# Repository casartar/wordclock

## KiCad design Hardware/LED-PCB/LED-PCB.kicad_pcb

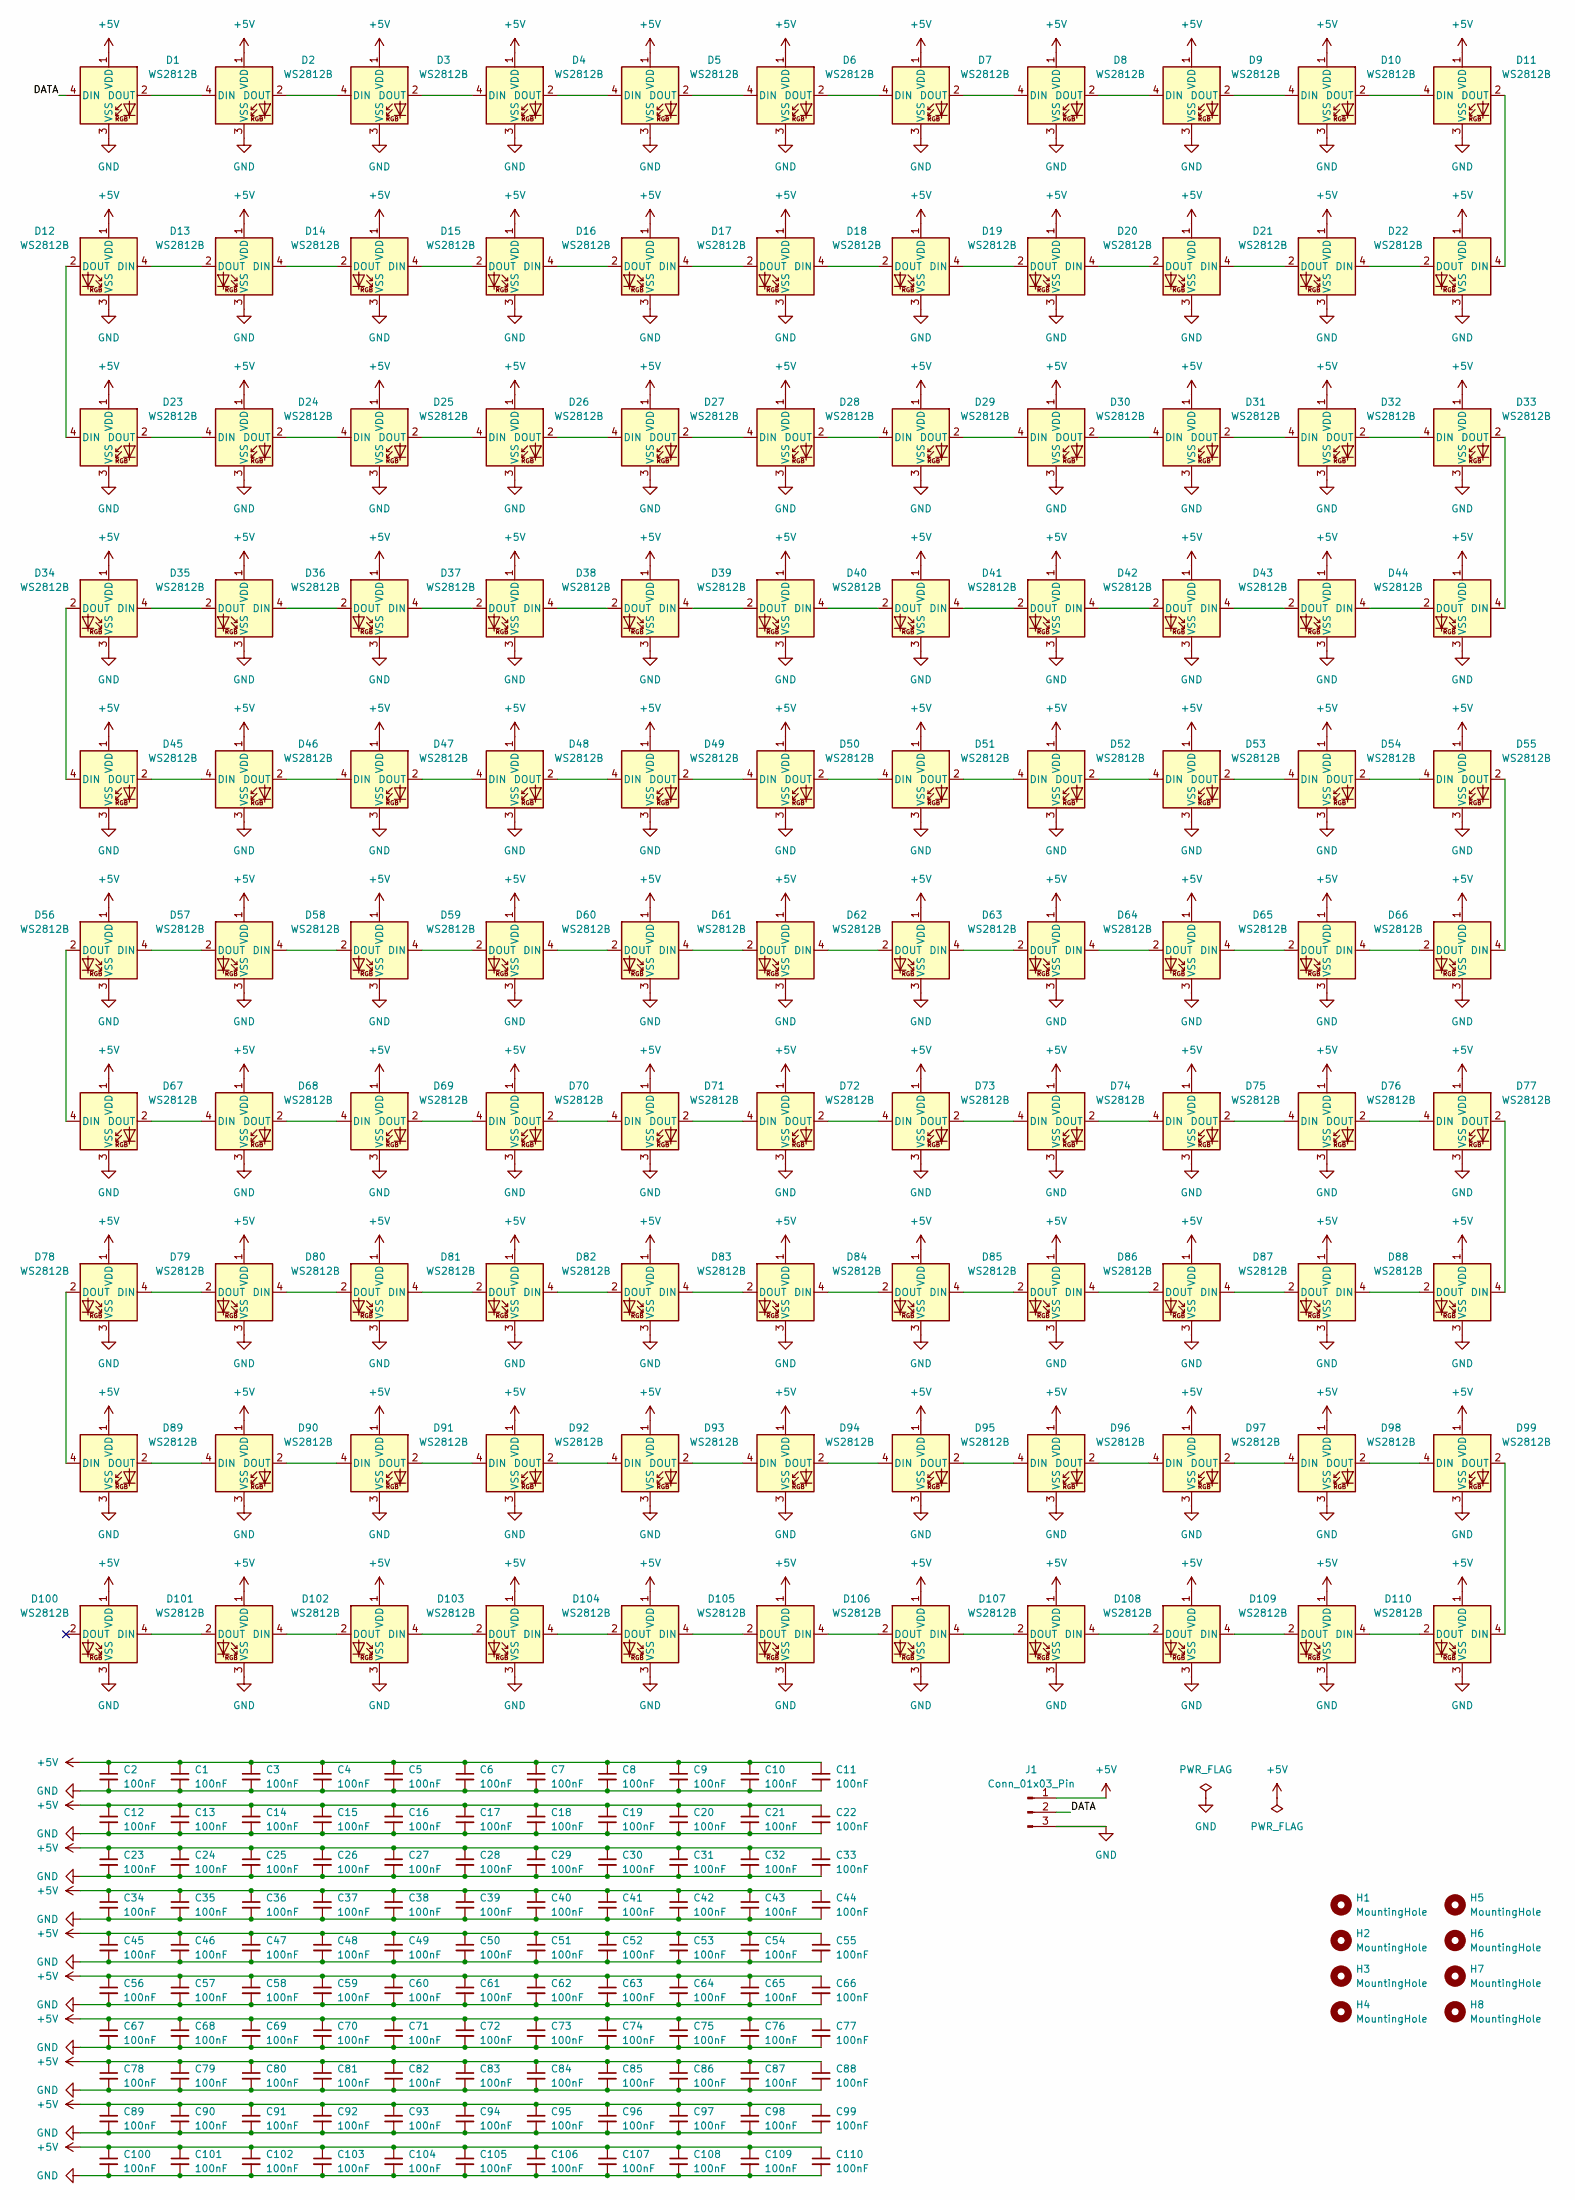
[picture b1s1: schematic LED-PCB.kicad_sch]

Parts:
C1, C2, C3, C4, C5, C6, C7, C8, C9, C10, C11, C12, C13, C14, C15, C16, C17, C18, C19, C20, C21, C22, C23, C24, C25, C26, C27, C28, C29, C30, C31, C32, C33, C34, C35, C36, C37, C38, C39, C40, C41, C42, C43, C44, C45, C46, C47, C48, C49, C50, C51, C52, C53, C54, C55, C56, C57, C58, C59, C60, C61, C62, C63, C64, C65, C66, C67, C68, C69, C70, C71, C72, C73, C74, C75, C76, C77, C78, C79, C80, C81, C82, C83, C84, C85, C86, C87, C88, C89, C90, C91, C92, C93, C94, C95, C96, C97, C98, C99, C100, C101, C102, C103, C104, C105, C106, C107, C108, C109, C110: 100nF; C_0805_2012Metric_Pad1.18x1.45mm_HandSolder
D1, D2, D3, D4, D5, D6, D7, D8, D9, D10, D11, D12, D13, D14, D15, D16, D17, D18, D19, D20, D21, D22, D23, D24, D25, D26, D27, D28, D29, D30, D31, D32, D33, D34, D35, D36, D37, D38, D39, D40, D41, D42, D43, D44, D45, D46, D47, D48, D49, D50, D51, D52, D53, D54, D55, D56, D57, D58, D59, D60, D61, D62, D63, D64, D65, D66, D67, D68, D69, D70, D71, D72, D73, D74, D75, D76, D77, D78, D79, D80, D81, D82, D83, D84, D85, D86, D87, D88, D89, D90, D91, D92, D93, D94, D95, D96, D97, D98, D99, D100, D101, D102, D103, D104, D105, D106, D107, D108, D109, D110: WS2812B; LED_WS2812B_PLCC4_5.0x5.0mm_P3.2mm
H1, H2, H3, H4, H5, H6, H7, H8: MountingHole; MountingHole_3.2mm_M3
J1: Conn_01x03_Pin; HDR-SMD_3P-P2.54-H-M_KH-2.54PH-1X3P-L13.5-WT

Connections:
+5V: C1.1, C2.1, C3.1, C4.1, C5.1, C6.1, C7.1, C8.1, C9.1, C10.1, C11.1, C12.1, C13.1, C14.1, C15.1, C16.1, C17.1, C18.1, C19.1, C20.1, C21.1, C22.1, C23.1, C24.1, C25.1, C26.1, C27.1, C28.1, C29.1, C30.1, C31.1, C32.1, C33.1, C34.1, C35.1, C36.1, C37.1, C38.1, C39.1, C40.1, C41.1, C42.1, C43.1, C44.1, C45.1, C46.1, C47.1, C48.1, C49.1, C50.1, C51.1, C52.1, C53.1, C54.1, C55.1, C56.1, C57.1, C58.1, C59.1, C60.1, C61.1, C62.1, C63.1, C64.1, C65.1, C66.1, C67.1, C68.1, C69.1, C70.1, C71.1, C72.1, C73.1, C74.1, C75.1, C76.1, C77.1, C78.1, C79.1, C80.1, C81.1, C82.1, C83.1, C84.1, C85.1, C86.1, C87.1, C88.1, C89.1, C90.1, C91.1, C92.1, C93.1, C94.1, C95.1, C96.1, C97.1, C98.1, C99.1, C100.1, C101.1, C102.1, C103.1, C104.1, C105.1, C106.1, C107.1, C108.1, C109.1, C110.1, D1.1 (VDD), D2.1 (VDD), D3.1 (VDD), D4.1 (VDD), D5.1 (VDD), D6.1 (VDD), D7.1 (VDD), D8.1 (VDD), D9.1 (VDD), D10.1 (VDD), D11.1 (VDD), D12.1 (VDD), D13.1 (VDD), D14.1 (VDD), D15.1 (VDD), D16.1 (VDD), D17.1 (VDD), D18.1 (VDD), D19.1 (VDD), D20.1 (VDD), D21.1 (VDD), D22.1 (VDD), D23.1 (VDD), D24.1 (VDD), D25.1 (VDD), D26.1 (VDD), D27.1 (VDD), D28.1 (VDD), D29.1 (VDD), D30.1 (VDD), D31.1 (VDD), D32.1 (VDD), D33.1 (VDD), D34.1 (VDD), D35.1 (VDD), D36.1 (VDD), D37.1 (VDD), D38.1 (VDD), D39.1 (VDD), D40.1 (VDD), D41.1 (VDD), D42.1 (VDD), D43.1 (VDD), D44.1 (VDD), D45.1 (VDD), D46.1 (VDD), D47.1 (VDD), D48.1 (VDD), D49.1 (VDD), D50.1 (VDD), D51.1 (VDD), D52.1 (VDD), D53.1 (VDD), D54.1 (VDD), D55.1 (VDD), D56.1 (VDD), D57.1 (VDD), D58.1 (VDD), D59.1 (VDD), D60.1 (VDD), D61.1 (VDD), D62.1 (VDD), D63.1 (VDD), D64.1 (VDD), D65.1 (VDD), D66.1 (VDD), D67.1 (VDD), D68.1 (VDD), D69.1 (VDD), D70.1 (VDD), D71.1 (VDD), D72.1 (VDD), D73.1 (VDD), D74.1 (VDD), D75.1 (VDD), D76.1 (VDD), D77.1 (VDD), D78.1 (VDD), D79.1 (VDD), D80.1 (VDD), D81.1 (VDD), D82.1 (VDD), D83.1 (VDD), D84.1 (VDD), D85.1 (VDD), D86.1 (VDD), D87.1 (VDD), D88.1 (VDD), D89.1 (VDD), D90.1 (VDD), D91.1 (VDD), D92.1 (VDD), D93.1 (VDD), D94.1 (VDD), D95.1 (VDD), D96.1 (VDD), D97.1 (VDD), D98.1 (VDD), D99.1 (VDD), D100.1 (VDD), D101.1 (VDD), D102.1 (VDD), D103.1 (VDD), D104.1 (VDD), D105.1 (VDD), D106.1 (VDD), D107.1 (VDD), D108.1 (VDD), D109.1 (VDD), D110.1 (VDD), J1.1
/DATA: D1.4 (DIN), J1.2
GND: C1.2, C2.2, C3.2, C4.2, C5.2, C6.2, C7.2, C8.2, C9.2, C10.2, C11.2, C12.2, C13.2, C14.2, C15.2, C16.2, C17.2, C18.2, C19.2, C20.2, C21.2, C22.2, C23.2, C24.2, C25.2, C26.2, C27.2, C28.2, C29.2, C30.2, C31.2, C32.2, C33.2, C34.2, C35.2, C36.2, C37.2, C38.2, C39.2, C40.2, C41.2, C42.2, C43.2, C44.2, C45.2, C46.2, C47.2, C48.2, C49.2, C50.2, C51.2, C52.2, C53.2, C54.2, C55.2, C56.2, C57.2, C58.2, C59.2, C60.2, C61.2, C62.2, C63.2, C64.2, C65.2, C66.2, C67.2, C68.2, C69.2, C70.2, C71.2, C72.2, C73.2, C74.2, C75.2, C76.2, C77.2, C78.2, C79.2, C80.2, C81.2, C82.2, C83.2, C84.2, C85.2, C86.2, C87.2, C88.2, C89.2, C90.2, C91.2, C92.2, C93.2, C94.2, C95.2, C96.2, C97.2, C98.2, C99.2, C100.2, C101.2, C102.2, C103.2, C104.2, C105.2, C106.2, C107.2, C108.2, C109.2, C110.2, D1.3 (VSS), D2.3 (VSS), D3.3 (VSS), D4.3 (VSS), D5.3 (VSS), D6.3 (VSS), D7.3 (VSS), D8.3 (VSS), D9.3 (VSS), D10.3 (VSS), D11.3 (VSS), D12.3 (VSS), D13.3 (VSS), D14.3 (VSS), D15.3 (VSS), D16.3 (VSS), D17.3 (VSS), D18.3 (VSS), D19.3 (VSS), D20.3 (VSS), D21.3 (VSS), D22.3 (VSS), D23.3 (VSS), D24.3 (VSS), D25.3 (VSS), D26.3 (VSS), D27.3 (VSS), D28.3 (VSS), D29.3 (VSS), D30.3 (VSS), D31.3 (VSS), D32.3 (VSS), D33.3 (VSS), D34.3 (VSS), D35.3 (VSS), D36.3 (VSS), D37.3 (VSS), D38.3 (VSS), D39.3 (VSS), D40.3 (VSS), D41.3 (VSS), D42.3 (VSS), D43.3 (VSS), D44.3 (VSS), D45.3 (VSS), D46.3 (VSS), D47.3 (VSS), D48.3 (VSS), D49.3 (VSS), D50.3 (VSS), D51.3 (VSS), D52.3 (VSS), D53.3 (VSS), D54.3 (VSS), D55.3 (VSS), D56.3 (VSS), D57.3 (VSS), D58.3 (VSS), D59.3 (VSS), D60.3 (VSS), D61.3 (VSS), D62.3 (VSS), D63.3 (VSS), D64.3 (VSS), D65.3 (VSS), D66.3 (VSS), D67.3 (VSS), D68.3 (VSS), D69.3 (VSS), D70.3 (VSS), D71.3 (VSS), D72.3 (VSS), D73.3 (VSS), D74.3 (VSS), D75.3 (VSS), D76.3 (VSS), D77.3 (VSS), D78.3 (VSS), D79.3 (VSS), D80.3 (VSS), D81.3 (VSS), D82.3 (VSS), D83.3 (VSS), D84.3 (VSS), D85.3 (VSS), D86.3 (VSS), D87.3 (VSS), D88.3 (VSS), D89.3 (VSS), D90.3 (VSS), D91.3 (VSS), D92.3 (VSS), D93.3 (VSS), D94.3 (VSS), D95.3 (VSS), D96.3 (VSS), D97.3 (VSS), D98.3 (VSS), D99.3 (VSS), D100.3 (VSS), D101.3 (VSS), D102.3 (VSS), D103.3 (VSS), D104.3 (VSS), D105.3 (VSS), D106.3 (VSS), D107.3 (VSS), D108.3 (VSS), D109.3 (VSS), D110.3 (VSS), J1.3
unnamed: D1.2 (DOUT), D2.4 (DIN)
unnamed: D2.2 (DOUT), D3.4 (DIN)
unnamed: D3.2 (DOUT), D4.4 (DIN)
unnamed: D4.2 (DOUT), D5.4 (DIN)
unnamed: D5.2 (DOUT), D6.4 (DIN)
unnamed: D6.2 (DOUT), D7.4 (DIN)
unnamed: D7.2 (DOUT), D8.4 (DIN)
unnamed: D8.2 (DOUT), D9.4 (DIN)
unnamed: D9.2 (DOUT), D10.4 (DIN)
unnamed: D10.2 (DOUT), D11.4 (DIN)
unnamed: D11.2 (DOUT), D22.4 (DIN)
unnamed: D12.4 (DIN), D13.2 (DOUT)
unnamed: D12.2 (DOUT), D23.4 (DIN)
unnamed: D13.4 (DIN), D14.2 (DOUT)
unnamed: D14.4 (DIN), D15.2 (DOUT)
unnamed: D15.4 (DIN), D16.2 (DOUT)
unnamed: D16.4 (DIN), D17.2 (DOUT)
unnamed: D17.4 (DIN), D18.2 (DOUT)
unnamed: D18.4 (DIN), D19.2 (DOUT)
unnamed: D19.4 (DIN), D20.2 (DOUT)
unnamed: D20.4 (DIN), D21.2 (DOUT)
unnamed: D21.4 (DIN), D22.2 (DOUT)
unnamed: D23.2 (DOUT), D24.4 (DIN)
unnamed: D24.2 (DOUT), D25.4 (DIN)
unnamed: D25.2 (DOUT), D26.4 (DIN)
unnamed: D26.2 (DOUT), D27.4 (DIN)
unnamed: D27.2 (DOUT), D28.4 (DIN)
unnamed: D28.2 (DOUT), D29.4 (DIN)
unnamed: D29.2 (DOUT), D30.4 (DIN)
unnamed: D30.2 (DOUT), D31.4 (DIN)
unnamed: D31.2 (DOUT), D32.4 (DIN)
unnamed: D32.2 (DOUT), D33.4 (DIN)
unnamed: D33.2 (DOUT), D44.4 (DIN)
unnamed: D34.4 (DIN), D35.2 (DOUT)
unnamed: D34.2 (DOUT), D45.4 (DIN)
unnamed: D35.4 (DIN), D36.2 (DOUT)
unnamed: D36.4 (DIN), D37.2 (DOUT)
unnamed: D37.4 (DIN), D38.2 (DOUT)
unnamed: D38.4 (DIN), D39.2 (DOUT)
unnamed: D39.4 (DIN), D40.2 (DOUT)
unnamed: D40.4 (DIN), D41.2 (DOUT)
unnamed: D41.4 (DIN), D42.2 (DOUT)
unnamed: D42.4 (DIN), D43.2 (DOUT)
unnamed: D43.4 (DIN), D44.2 (DOUT)
unnamed: D45.2 (DOUT), D46.4 (DIN)
unnamed: D46.2 (DOUT), D47.4 (DIN)
unnamed: D47.2 (DOUT), D48.4 (DIN)
unnamed: D48.2 (DOUT), D49.4 (DIN)
unnamed: D49.2 (DOUT), D50.4 (DIN)
unnamed: D50.2 (DOUT), D51.4 (DIN)
unnamed: D51.2 (DOUT), D52.4 (DIN)
unnamed: D52.2 (DOUT), D53.4 (DIN)
unnamed: D53.2 (DOUT), D54.4 (DIN)
unnamed: D54.2 (DOUT), D55.4 (DIN)
unnamed: D55.2 (DOUT), D66.4 (DIN)
unnamed: D56.4 (DIN), D57.2 (DOUT)
unnamed: D56.2 (DOUT), D67.4 (DIN)
unnamed: D57.4 (DIN), D58.2 (DOUT)
unnamed: D58.4 (DIN), D59.2 (DOUT)
unnamed: D59.4 (DIN), D60.2 (DOUT)
unnamed: D60.4 (DIN), D61.2 (DOUT)
unnamed: D61.4 (DIN), D62.2 (DOUT)
unnamed: D62.4 (DIN), D63.2 (DOUT)
unnamed: D63.4 (DIN), D64.2 (DOUT)
unnamed: D64.4 (DIN), D65.2 (DOUT)
unnamed: D65.4 (DIN), D66.2 (DOUT)
unnamed: D67.2 (DOUT), D68.4 (DIN)
unnamed: D68.2 (DOUT), D69.4 (DIN)
unnamed: D69.2 (DOUT), D70.4 (DIN)
unnamed: D70.2 (DOUT), D71.4 (DIN)
unnamed: D71.2 (DOUT), D72.4 (DIN)
unnamed: D72.2 (DOUT), D73.4 (DIN)
unnamed: D73.2 (DOUT), D74.4 (DIN)
unnamed: D74.2 (DOUT), D75.4 (DIN)
unnamed: D75.2 (DOUT), D76.4 (DIN)
unnamed: D76.2 (DOUT), D77.4 (DIN)
unnamed: D77.2 (DOUT), D88.4 (DIN)
unnamed: D78.4 (DIN), D79.2 (DOUT)
unnamed: D78.2 (DOUT), D89.4 (DIN)
unnamed: D79.4 (DIN), D80.2 (DOUT)
unnamed: D80.4 (DIN), D81.2 (DOUT)
unnamed: D81.4 (DIN), D82.2 (DOUT)
unnamed: D82.4 (DIN), D83.2 (DOUT)
unnamed: D83.4 (DIN), D84.2 (DOUT)
unnamed: D84.4 (DIN), D85.2 (DOUT)
unnamed: D85.4 (DIN), D86.2 (DOUT)
unnamed: D86.4 (DIN), D87.2 (DOUT)
unnamed: D87.4 (DIN), D88.2 (DOUT)
unnamed: D89.2 (DOUT), D90.4 (DIN)
unnamed: D90.2 (DOUT), D91.4 (DIN)
unnamed: D91.2 (DOUT), D92.4 (DIN)
unnamed: D92.2 (DOUT), D93.4 (DIN)
unnamed: D93.2 (DOUT), D94.4 (DIN)
unnamed: D94.2 (DOUT), D95.4 (DIN)
unnamed: D95.2 (DOUT), D96.4 (DIN)
unnamed: D96.2 (DOUT), D97.4 (DIN)
unnamed: D97.2 (DOUT), D98.4 (DIN)
unnamed: D98.2 (DOUT), D99.4 (DIN)
unnamed: D100.4 (DIN), D101.2 (DOUT)
unnamed: D101.4 (DIN), D102.2 (DOUT)
unnamed: D102.4 (DIN), D103.2 (DOUT)
unnamed: D103.4 (DIN), D104.2 (DOUT)
unnamed: D104.4 (DIN), D105.2 (DOUT)
unnamed: D105.4 (DIN), D106.2 (DOUT)
unnamed: D106.4 (DIN), D107.2 (DOUT)
unnamed: D107.4 (DIN), D108.2 (DOUT)
unnamed: D108.4 (DIN), D109.2 (DOUT)
unnamed: D109.4 (DIN), D110.2 (DOUT)
unnamed: D99.2 (DOUT), D110.4 (DIN)

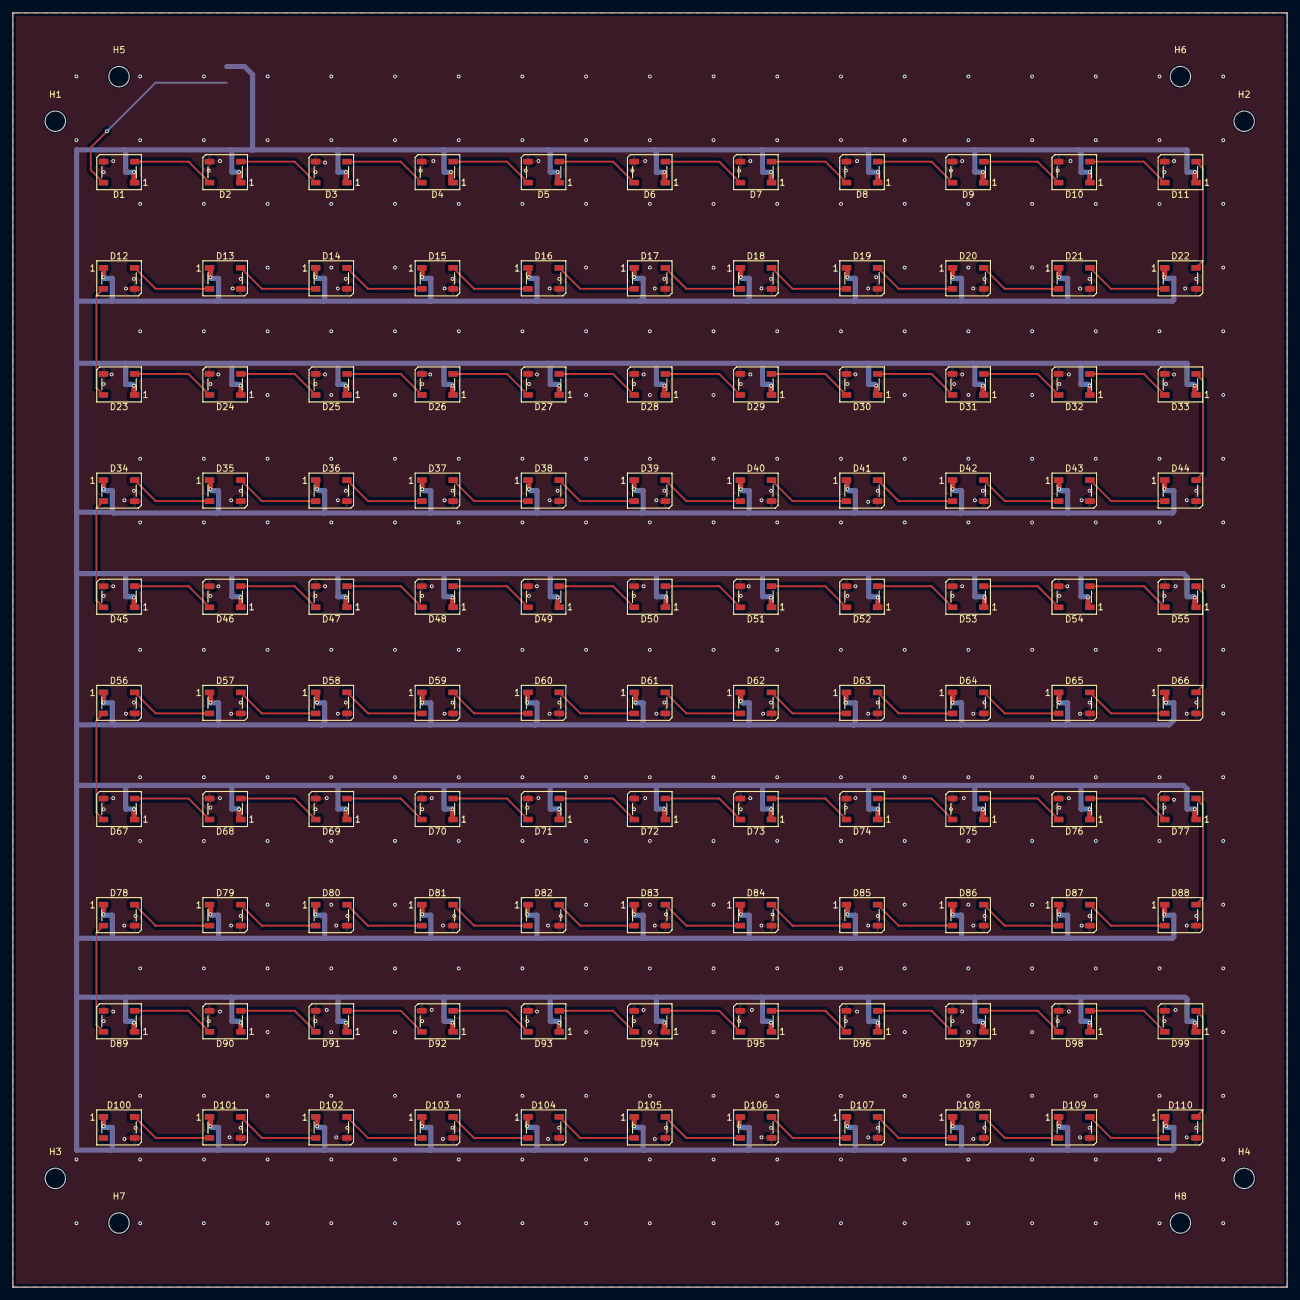
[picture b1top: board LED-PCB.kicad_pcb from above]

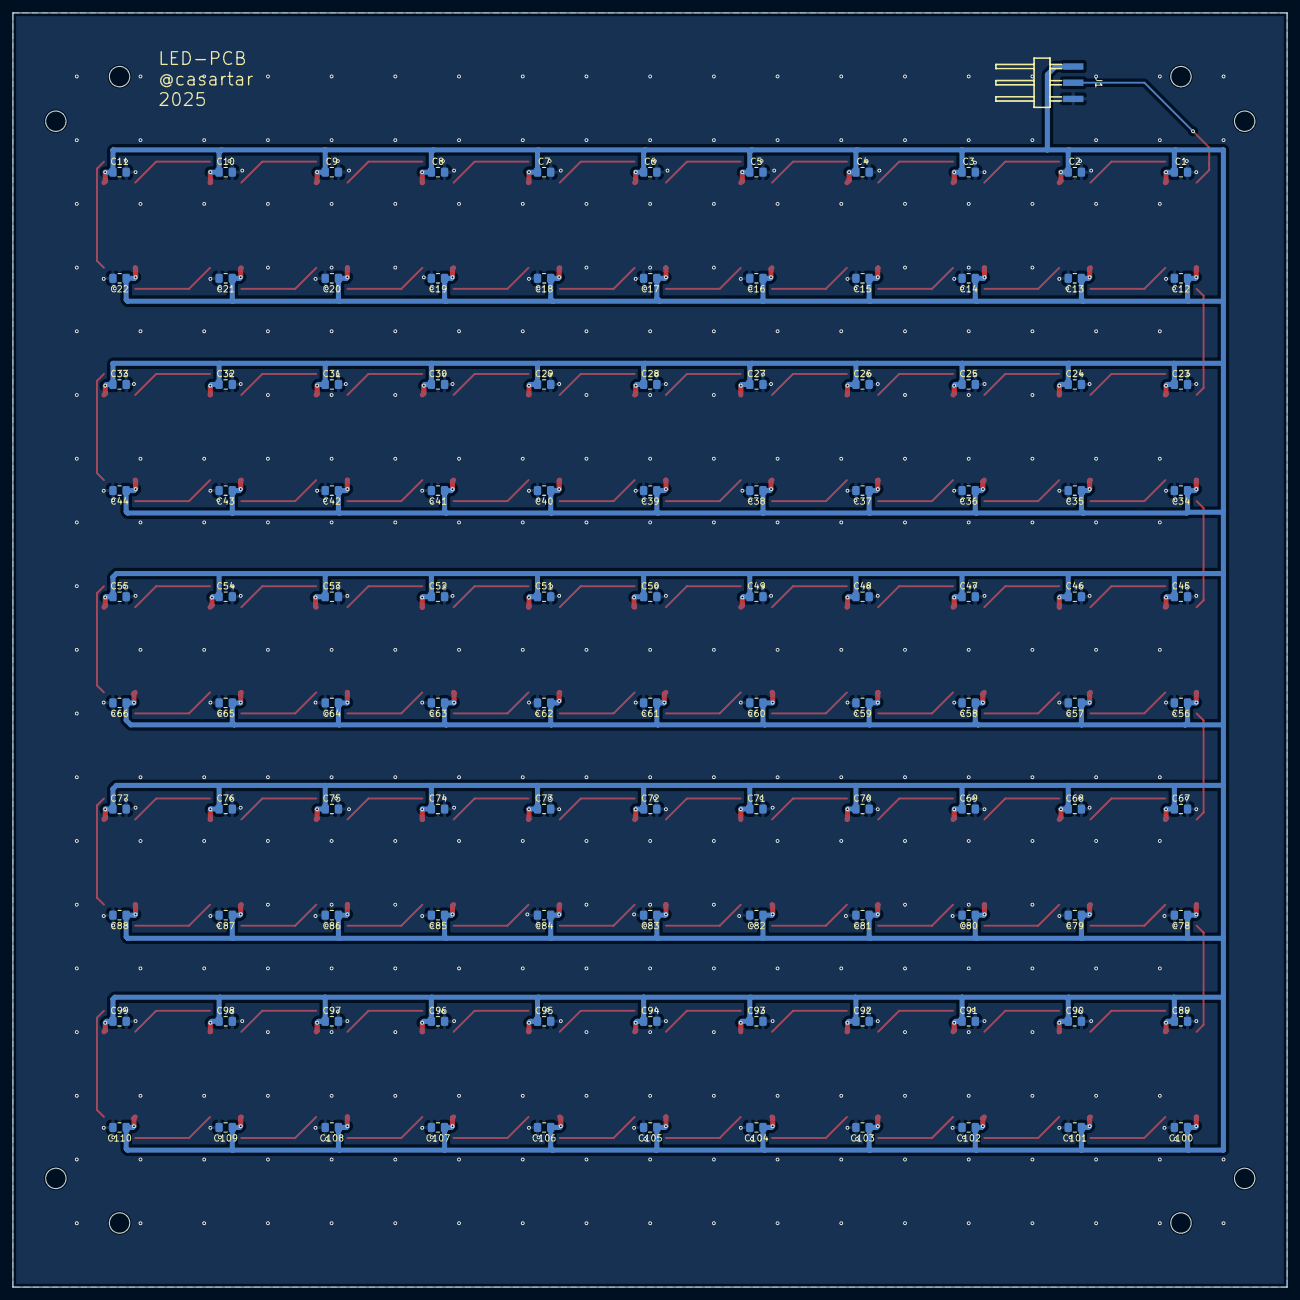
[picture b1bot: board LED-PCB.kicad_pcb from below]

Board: 2 copper layers, 200.0 x 200.0 mm, 229 parts (111 on the bottom side), 112 nets.

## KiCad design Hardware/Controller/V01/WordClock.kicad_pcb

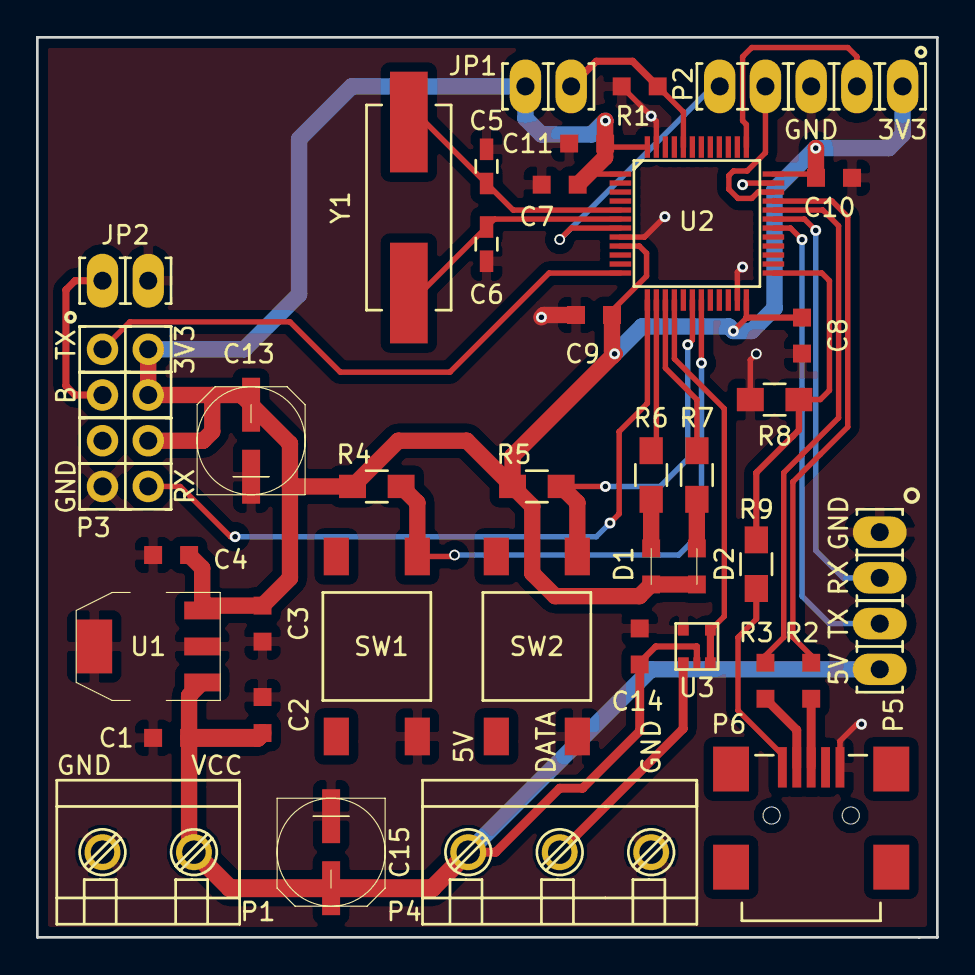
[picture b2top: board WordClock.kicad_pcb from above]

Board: 2 copper layers, 50.0 x 50.0 mm, 39 parts (0 on the bottom side), 28 nets.

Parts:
C1, C4, C7, C8, C9, C10, C11, C14: 100n; C_0805_HandSoldering
C2, C3: 1u; C_0805_HandSoldering
C5, C6: 16p; C_0603_HandSoldering
C13, C15: 100u; c_elec_6.3x5.7
D1, D2: LED; LED_0805
JP1, JP2: Jumper_NO_Small; PIN_HEADER_01x02
P1: CONN_01X02; CONN_RM5,08_2PIN
P2: CONN_01X05; PIN_HEADER_01x05
P3: CONN_02X04; PIN_HEADER_02x04
P4: CONN_01X03; CONN_RM5,08_3PIN
P5: CONN_01X04; PIN_HEADER_01x04
P6: USB_OTG; MINI USB 2.0 SMD
R1, R4, R5: 10k; R_0805_HandSoldering
R2, R3: 27; R_0805_HandSoldering
R6, R7: 1k; R_0805_HandSoldering
R8: 15k; R_0805_HandSoldering
R9: 22k; R_0805_HandSoldering
SW1, SW2: SW_PUSH; Kurzhubtaster_SMD
U1: MCP1825S; SOT-223
U2: STM32F072CB; LQFP48
U3: 74HCT1G08GW-Q100; SOT353-1
Y1: Crystal_Small; Quarz_SMD

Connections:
+3V3: C3.1, C4.1, C7.1, C8.1, C9.1, C10.1, C11.1, C13.1, D1.2, D2.2, JP1.1, P2.1, P3.2, P3.4, P3.6, R4.2, R5.2, U1.3, U2.1, U2.9, U2.24, U2.36, U2.48
+5V: C1.1, C2.1, C14.1, C15.1, P1.2, P4.1, P5.4, U1.1, U3.5
/USART1_RX: P5.2, U2.31
/USART1_TX: P5.3, U2.30
/USART2_RX: P3.8, U2.13
/USART2_TX: P3.1, U2.12
/USB_DM: R3.2, U2.32
/USB_DP: R2.2, U2.33
GND: C1.2, C2.2, C3.2, C4.2, C5.1, C6.2, C7.2, C8.2, C9.2, C10.2, C11.2, C13.2, C14.2, C15.2, JP2.2, P1.1, P2.3, P3.7, P4.3, P5.1, P6.5, R1.2, R8.1, SW1.2, SW2.2, U1.2, U1.4, U2.8, U2.23, U2.35, U2.47, U3.3
NRST: P2.5, U2.7
unnamed: C5.2, U2.5, Y1.1
unnamed: C6.1, U2.6, Y1.2
unnamed: D1.1, R6.1
unnamed: D2.1, R7.1
unnamed: JP1.2, R1.1, U2.44
unnamed: JP2.1, P3.3
unnamed: P4.2, U3.4
unnamed: P6.1, R9.2
unnamed: P6.2, R3.1
unnamed: P6.3, R2.1
unnamed: R4.1, SW1.1, U2.19
unnamed: R5.1, SW2.1, U2.18
unnamed: R6.2, U2.14
unnamed: R7.2, U2.15
unnamed: U2.16, U3.1, U3.2
SWCLK: P2.2, U2.37
SWDIO: P2.4, U2.34
USB_ACTIVE: R8.2, R9.1, U2.25

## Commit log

2016-07-24 Changed Debug device to ST-LinkV2
2016-07-24 Project realted changes
2016-07-24 Some changes in esp8266 module
    stabalized program sequence
2016-07-25 emulated eeprom added
2016-07-26 LibreCAD letter matrix added
2016-09-29 Basic command handler added
    in and output of ssid and password over uart
2016-10-02 remove unused includes, update gitignore
2016-10-02 Prallel Build enabled
2016-10-02 Add decoder for time structure
    - decode time structure from timer module
    - add mask for german wordclock
    - minor changes in led_matrix
2016-10-02 Command handler implemented
2016-10-02 Cleanup of main and remove sscanf in cmdHandler
2016-10-02 Add small fixes for displaying
    - add "Ein" as another word
    - add WLAN init
    - add summertime
    - hardcode WLAN login
2016-10-02 Init word clock with config values
    - set default brightness to 50
    - use colours from config to init word clock
2016-10-03 major changes
    - change congif struct
    - extend command handler for word colour
    - show red lights as long as there is no valid timestamp
    - extend wordclock init
    - new case for 1 am
2016-10-03 extend cmdHandler - add display for word color config
2016-10-05 3D model of LED matrix added
    i deceded to name this thing - with the drillings - LED matrix
2025-01-06 move V01 directory inside Controller directory
2025-01-06 add LED-PCB project with schematic
2025-01-08 led placed
2025-01-09 placed capacitors
2025-01-09 add gnd vias
2025-01-16 change connector and place mounting holes
2025-02-02 add Spacer Drawing
